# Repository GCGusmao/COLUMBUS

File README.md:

# COLUMBUS

README ainda em construção.

Desenvolvimento de um sistema de monitoramento para veículos híbridos, baseado em microcontrolador Atmel AVR. Foi desenvolvida a solução completa de hardware, software e soluções mecânicas.

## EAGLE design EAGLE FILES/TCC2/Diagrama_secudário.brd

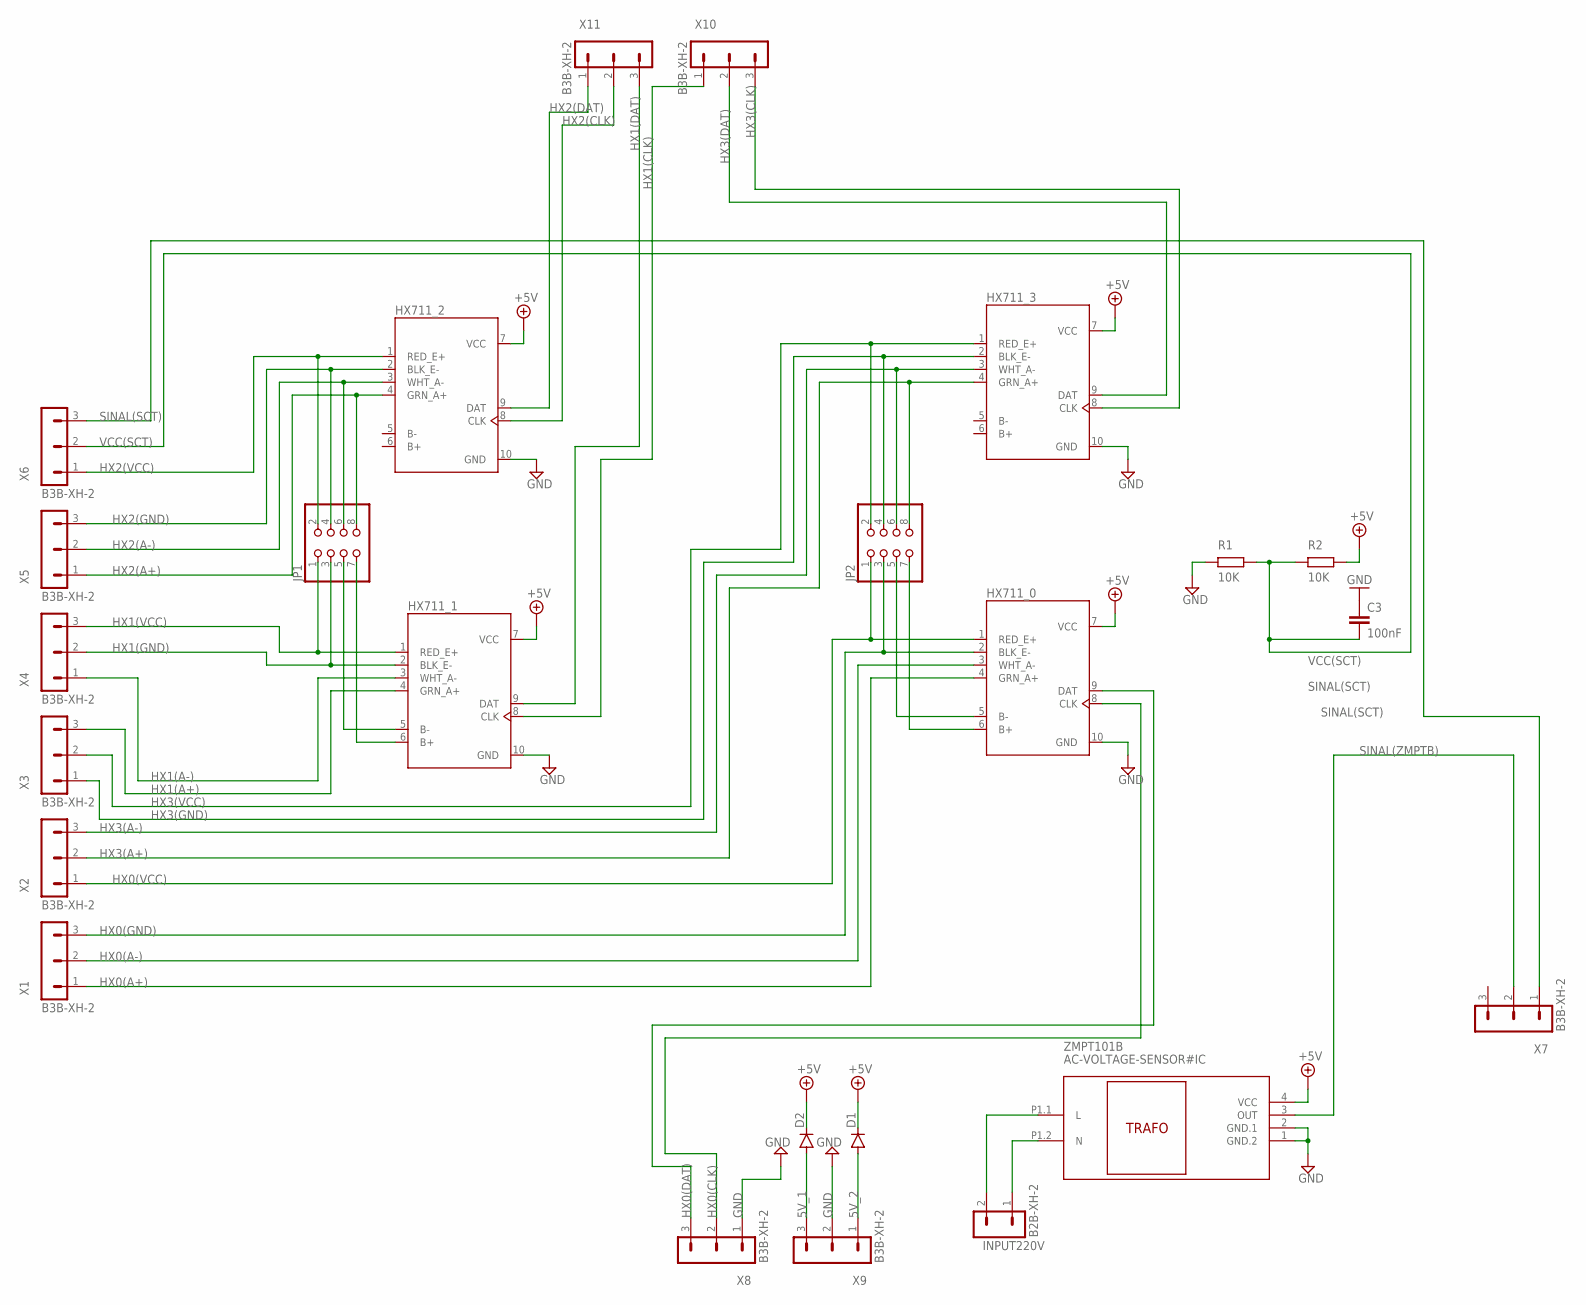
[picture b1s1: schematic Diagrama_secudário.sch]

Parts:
C3: 100nF; C050-025X075
D1: 1N4148DO35-7; DO35-7
D2: 1; DO35-7
HX711_0, HX711_1, HX711_2, HX711_3: HX711MODULO
INPUT220V: B2B-XH-2; B2B-XH-A
JP1, JP2: PINHD-2X4; 2X04
R1, R2: 10K; 1/4W-0.41K
X1, X2, X3, X4, X5, X6, X7, X8, X9, X10, X11: B3B-XH-2; B3B-XH-A
ZMPT101B: AC-VOLTAGE-SENSOR#IC

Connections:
5V_1: D2.A, X9.3
5V_2: D1.A, X9.1
+5V: D1.C, D2.C, HX711_0.7 (VCC), HX711_1.7 (VCC), HX711_2.7 (VCC), HX711_3.7 (VCC), R2.2, ZMPT101B.4 (VCC)
GND: C3.1, HX711_0.10 (GND), HX711_1.10 (GND), HX711_2.10 (GND), HX711_3.10 (GND), R1.1, X8.1, X9.2, ZMPT101B.1 (GND.2), ZMPT101B.2 (GND.1)
HX0(A+): HX711_0.4 (GRN_A+), X1.1
HX0(A-): HX711_0.3 (WHT_A-), X1.2
HX0(B+): HX711_0.6 (B+), JP2.7
HX0(B-): HX711_0.5 (B-), JP2.5
HX0(CLK): HX711_0.8 (CLK), X8.2
HX0(DAT): HX711_0.9 (DAT), X8.3
HX0(GND): HX711_0.2 (BLK_E-), JP2.3, X1.3
HX0(VCC): HX711_0.1 (RED_E+), JP2.1, X2.1
HX1(A+): HX711_1.4 (GRN_A+), X3.3
HX1(A-): HX711_1.3 (WHT_A-), X4.1
HX1(B+): HX711_1.6 (B+), JP1.7
HX1(B-): HX711_1.5 (B-), JP1.5
HX1(CLK): HX711_1.8 (CLK), X10.1
HX1(DAT): HX711_1.9 (DAT), X11.3
HX1(GND): HX711_1.2 (BLK_E-), JP1.3, X4.2
HX1(VCC): HX711_1.1 (RED_E+), JP1.1, X4.3
HX2(A+): HX711_2.4 (GRN_A+), JP1.8, X5.1
HX2(A-): HX711_2.3 (WHT_A-), JP1.6, X5.2
HX2(CLK): HX711_2.8 (CLK), X11.2
HX2(DAT): HX711_2.9 (DAT), X11.1
HX2(GND): HX711_2.2 (BLK_E-), JP1.4, X5.3
HX2(VCC): HX711_2.1 (RED_E+), JP1.2, X6.1
HX3(A+): HX711_3.4 (GRN_A+), JP2.8, X2.2
HX3(A-): HX711_3.3 (WHT_A-), JP2.6, X2.3
HX3(CLK): HX711_3.8 (CLK), X10.3
HX3(DAT): HX711_3.9 (DAT), X10.2
HX3(GND): HX711_3.2 (BLK_E-), JP2.4, X3.1
HX3(VCC): HX711_3.1 (RED_E+), JP2.2, X3.2
unnamed: INPUT220V.1, ZMPT101B.P1.2 (N)
unnamed: INPUT220V.2, ZMPT101B.P1.1 (L)
SINAL(SCT): X6.3, X7.1
SINAL(ZMPTB): X7.2, ZMPT101B.3 (OUT)
VCC(SCT): C3.2, R1.2, R2.1, X6.2

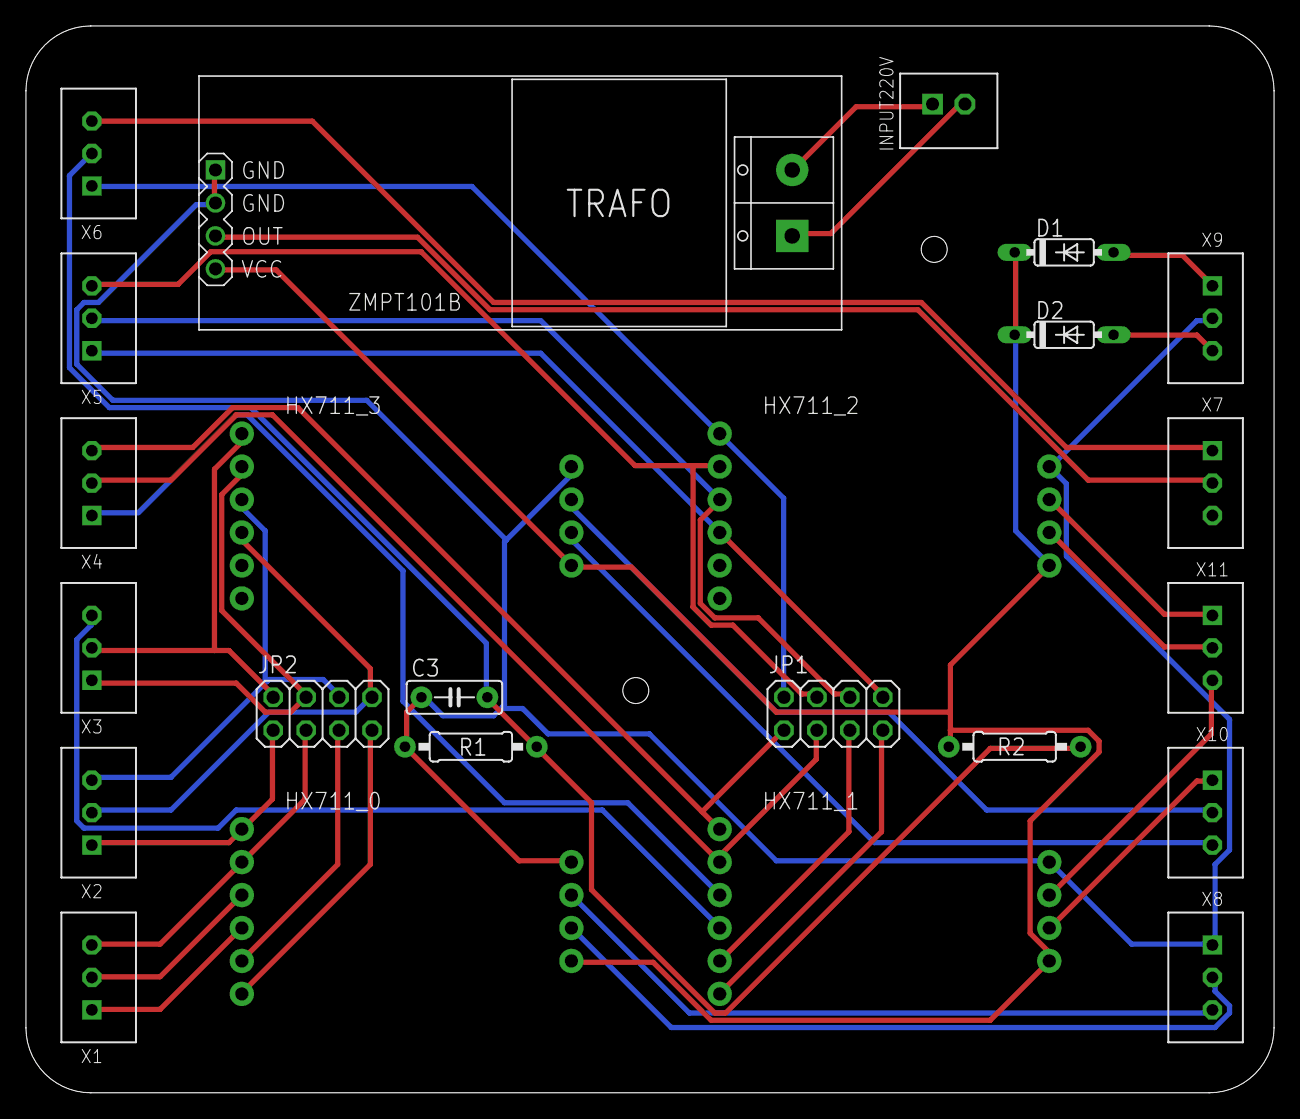
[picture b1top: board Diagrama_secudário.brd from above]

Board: 2 copper layers, 96.2 x 82.2 mm, 24 parts (0 on the bottom side), 37 nets.

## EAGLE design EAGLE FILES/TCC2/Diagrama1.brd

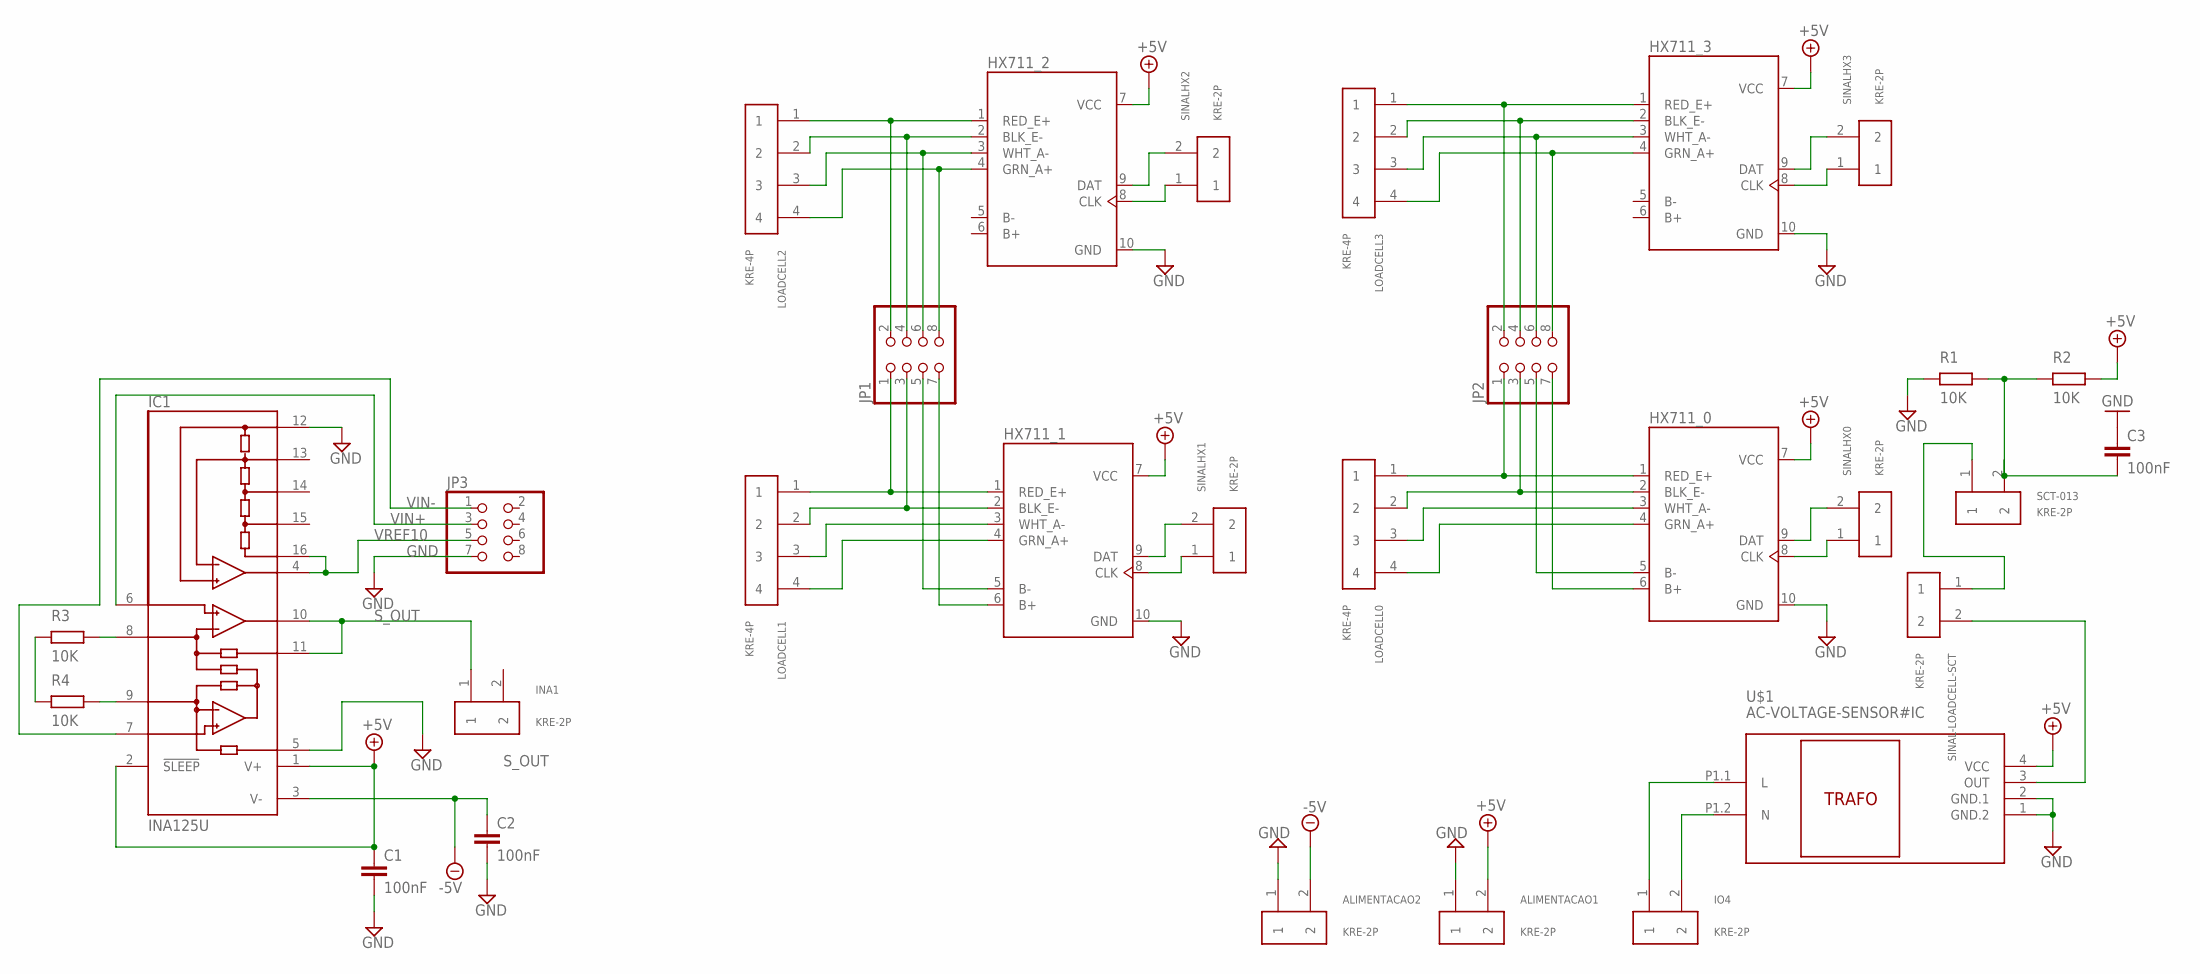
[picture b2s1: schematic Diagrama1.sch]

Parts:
ALIMENTACAO1, ALIMENTACAO2: KRE-2P
C1, C2, C3: 100nF; C050-025X075
HX711_0, HX711_1, HX711_2, HX711_3: HX711MODULO
IC1: INA125U; SO16-1
INA1: KRE-2P
IO4: KRE-2P
JP1, JP2, JP3: PINHD-2X4; 2X04
LOADCELL0, LOADCELL1, LOADCELL2, LOADCELL3: KRE-4P
R1, R2, R3, R4: 10K; 1/4W-0.41K
SCT-013: KRE-2P
SINAL-LOADCELL-SCT: KRE-2P
SINALHX0, SINALHX1, SINALHX2, SINALHX3: KRE-2P
U$1: AC-VOLTAGE-SENSOR#IC

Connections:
+5V: ALIMENTACAO1.2, C1.1, HX711_0.7 (VCC), HX711_1.7 (VCC), HX711_2.7 (VCC), HX711_3.7 (VCC), IC1.1 (V+), IC1.2 (!SLEEP), R2.2, U$1.4 (VCC)
-5V: ALIMENTACAO2.2, C2.1, IC1.3 (V-)
GND: ALIMENTACAO1.1, ALIMENTACAO2.1, C1.2, C2.2, C3.1, HX711_0.10 (GND), HX711_1.10 (GND), HX711_2.10 (GND), HX711_3.10 (GND), IC1.5 (REF), IC1.12 (REFCOM), JP3.7, R1.1, U$1.1 (GND.2), U$1.2 (GND.1)
unnamed: IO4.2, U$1.P1.2 (N)
unnamed: IO4.1, U$1.P1.1 (L)
unnamed: HX711_0.1 (RED_E+), JP2.1, LOADCELL0.1
unnamed: HX711_0.4 (GRN_A+), LOADCELL0.4
unnamed: HX711_0.2 (BLK_E-), JP2.3, LOADCELL0.2
unnamed: HX711_1.1 (RED_E+), JP1.1, LOADCELL1.1
unnamed: HX711_0.3 (WHT_A-), LOADCELL0.3
unnamed: HX711_1.2 (BLK_E-), JP1.3, LOADCELL1.2
unnamed: HX711_1.3 (WHT_A-), LOADCELL1.3
unnamed: C3.2, R1.2, R2.1, SCT-013.2
unnamed: HX711_0.9 (DAT), SINALHX0.2
unnamed: HX711_0.8 (CLK), SINALHX0.1
unnamed: HX711_1.5 (B-), JP1.5
unnamed: HX711_1.4 (GRN_A+), LOADCELL1.4
unnamed: SINAL-LOADCELL-SCT.2, U$1.3 (OUT)
unnamed: HX711_1.9 (DAT), SINALHX1.2
unnamed: HX711_1.8 (CLK), SINALHX1.1
unnamed: HX711_2.1 (RED_E+), JP1.2, LOADCELL2.1
unnamed: HX711_2.2 (BLK_E-), JP1.4, LOADCELL2.2
unnamed: HX711_2.3 (WHT_A-), JP1.6, LOADCELL2.3
unnamed: HX711_2.4 (GRN_A+), JP1.8, LOADCELL2.4
unnamed: HX711_2.9 (DAT), SINALHX2.2
unnamed: HX711_2.8 (CLK), SINALHX2.1
unnamed: HX711_3.1 (RED_E+), JP2.2, LOADCELL3.1
unnamed: HX711_3.2 (BLK_E-), JP2.4, LOADCELL3.2
unnamed: HX711_3.3 (WHT_A-), JP2.6, LOADCELL3.3
unnamed: HX711_3.4 (GRN_A+), JP2.8, LOADCELL3.4
unnamed: HX711_3.9 (DAT), SINALHX3.2
unnamed: HX711_3.8 (CLK), SINALHX3.1
unnamed: SCT-013.1, SINAL-LOADCELL-SCT.1
unnamed: HX711_1.6 (B+), JP1.7
unnamed: HX711_0.5 (B-), JP2.5
unnamed: HX711_0.6 (B+), JP2.7
unnamed: R3.1, R4.1
unnamed: IC1.9 (RG), R4.2
unnamed: IC1.8 (RG), R3.2
S_OUT: IC1.10 (OUT), IC1.11 (SENSE), INA1.1
VIN+: IC1.6 (+IN), JP3.3
VIN-: IC1.7 (-IN), JP3.1
VREF10: IC1.4 (REFOUT), IC1.16 (REF10), JP3.5

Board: 2 copper layers, 30 parts (0 on the bottom side), 43 nets, no tracks yet.

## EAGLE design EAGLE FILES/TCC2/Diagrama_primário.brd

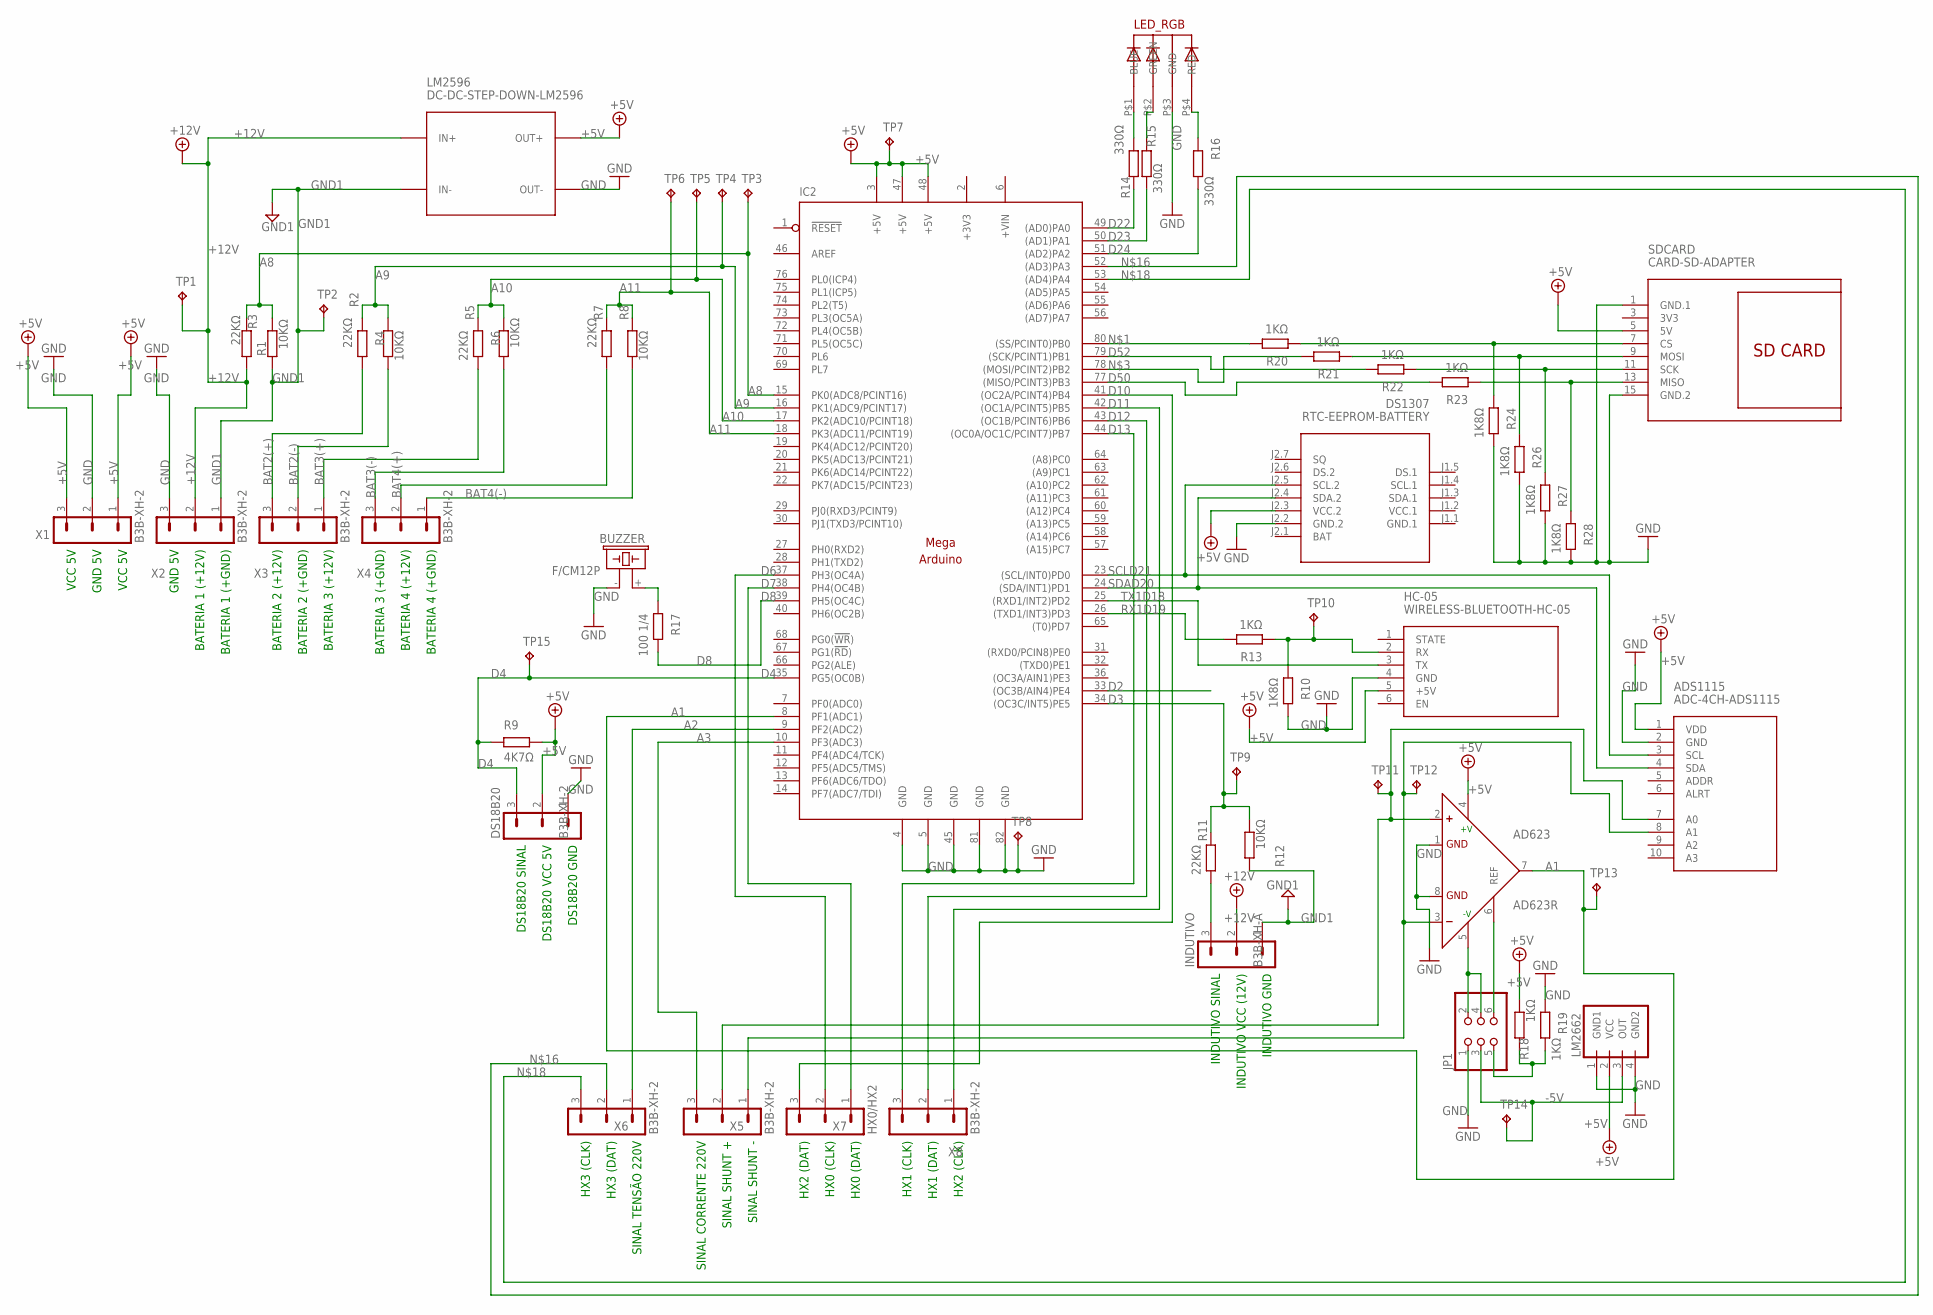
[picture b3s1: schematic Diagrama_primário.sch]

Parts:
AD623: AD623R; SO8
ADS1115: ADC-4CH-ADS1115
BUZZER: F/CM12P
DS18B20: B3B-XH-2; B3B-XH-A
DS1307: RTC-EEPROM-BATTERY
HC-05: WIRELESS-BLUETOOTH-HC-05
IC2: MEGAARDUINO_11; MEGA_ARDUINO_1
INDUTIVO: B3B-XH-A
JP1: PINHD-2X3; 2X03
LED_RGB: 5MMRGBLED; LED5MMRGB
LM2596: DC-DC-STEP-DOWN-LM2596
LM2662: LM2662
R1, R4, R6, R8, R12: 10KΩ; 1/4W-0.41K
R2, R3, R5, R7, R11: 22KΩ; 1/4W-0.41K
R9: 4K7Ω; 1/4W-0.41K
R10, R24, R26, R27, R28: 1K8Ω; 1/4W-0.41K
R13, R18, R19, R20, R21, R22, R23: 1KΩ; 1/4W-0.41K
R14, R15, R16: 330Ω; 1/4W-0.41K
R17: 100 1/4; 1/4W-0.41K
SDCARD: CARD-SD-ADAPTER
TP1, TP2, TP3, TP4, TP5, TP6, TP7, TP8, TP9, TP10, TP11, TP12, TP13, TP14, TP15: TPB1,27; B1,27
X1, X2, X3, X4, X5, X6, X8: B3B-XH-2; B3B-XH-A
X7: HX0/HX2; B3B-XH-A

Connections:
3V3: SDCARD.3 (3V3)
+3V3: IC2.2 (+3V3)
+5V: AD623.4 (+V), ADS1115.1 (VDD), DS18B20.2, DS1307.J2.3 (VCC.2), HC-05.5 (+5V), IC2.3 (+5V), IC2.47 (+5V), IC2.48 (+5V), LM2596.OUT+, LM2662.2 (VCC), R9.2, R18.1, SDCARD.5 (5V), TP7.TP, X1.1, X1.3
+12V: INDUTIVO.2, LM2596.IN+, R3.2, TP1.TP, X2.2
+VIN: IC2.6 (+VIN)
-5V: JP1.3, LM2662.3 (OUT), TP14.TP
A1: AD623.7 (OUT), IC2.8 (PF1(ADC1)), TP13.TP
A2: IC2.9 (PF2(ADC2)), X6.1
A3: IC2.10 (PF3(ADC3)), X5.3
A8: IC2.15 (PK0(ADC8/PCINT16)), R1.1, R3.1, TP3.TP
A9: IC2.16 (PK1(ADC9/PCINT17)), R2.1, R4.1, TP4.TP
A10: IC2.17 (PK2(ADC10/PCINT18)), R5.1, R6.1, TP5.TP
A11: IC2.18 (PK3(ADC11/PCINT19)), R7.1, R8.1, TP6.TP
BAT2(+): R2.2, X3.3
BAT2(-): R4.2, X3.2
BAT3(+): R5.2, X3.1
BAT3(-): R6.2, X4.3
BAT4(+): R7.2, X4.2
BAT4(-): R8.2, X4.1
D2: IC2.33 ((OC3B/AIN4)PE4)
D3: IC2.34 ((OC3C/INT5)PE5), R11.1, R12.1, TP9.TP
D4: DS18B20.3, IC2.35 (PG5(OC0B)), R9.1, TP15.TP
D6: IC2.37 (PH3(OC4A)), X7.2
D7: IC2.38 (PH4(OC4B)), X7.1
D8: IC2.39 (PH5(OC4C)), R17.2
D10: IC2.41 ((OC2A/PCINT4)PB4), X7.3
D11: IC2.42 ((OC1A/PCINT5)PB5), X8.1
D12: IC2.43 ((OC1B/PCINT6)PB6), X8.2
D13: IC2.44 ((OC0A/OC1C/PCINT7)PB7), X8.3
D22: IC2.49 ((AD0)PA0), R14.2
D23: IC2.50 ((AD1)PA1), R15.2
D24: IC2.51 ((AD2)PA2), R16.2
D50: IC2.77 ((MISO/PCINT3)PB3), R23.2
D51: R21.1, R26.1, SDCARD.9 (MOSI)
D52: IC2.79 ((SCK/PCINT1)PB1), R22.2
D53: R20.1, R24.1, SDCARD.7 (CS)
GND: AD623.1 (RG), AD623.8 (RG), ADS1115.2 (GND), BUZZER.- (2), DS18B20.1, DS1307.J2.2 (GND.2), HC-05.4 (GND), IC2.4 (GND), IC2.5 (GND), IC2.45 (GND), IC2.81 (GND), IC2.82 (GND), JP1.1, LED_RGB.P$3 (GND), LM2596.OUT-, LM2662.1 (GND1), LM2662.4 (GND2), R10.2, R19.1, R24.2, R26.2, R27.2, R28.2, SDCARD.1 (GND.1), SDCARD.15 (GND.2), TP8.TP, X1.2, X2.3
GND1: INDUTIVO.1, LM2596.IN-, R1.2, R12.2, TP2.TP, X2.1
GND.1: DS1307.J1.1 (GND.1)
unnamed: IC2.80 ((SS/PCINT0)PB0), R20.2
unnamed: INDUTIVO.3, R11.2
unnamed: IC2.78 ((MOSI/PCINT2)PB2), R21.2
unnamed: HC-05.2 (RX), R10.1, R13.1, TP10.TP
unnamed: LED_RGB.P$1 (BLUE), R14.1
unnamed: LED_RGB.P$2 (GREEN), R15.1
unnamed: LED_RGB.P$4 (RED), R16.1
unnamed: R22.1, R27.1, SDCARD.11 (SCK)
unnamed: R23.1, R28.1, SDCARD.13 (MISO)
unnamed: IC2.52 ((AD3)PA3), X6.2
unnamed: BUZZER.+ (1), R17.1
unnamed: IC2.53 ((AD4)PA4), X6.3
unnamed: AD623.3 (-), ADS1115.8 (A1), TP12.TP, X5.1
unnamed: AD623.2 (+), ADS1115.7 (A0), TP11.TP, X5.2
unnamed: AD623.5 (-V), JP1.2, JP1.4
unnamed: AD623.6 (REF), JP1.6
RX1D19: IC2.26 ((TXD1/INT3)PD3), R13.2
SCLD21: ADS1115.3 (SCL), DS1307.J2.5 (SCL.2), IC2.23 ((SCL/INT0)PD0)
SDAD20: ADS1115.4 (SDA), DS1307.J2.4 (SDA.2), IC2.24 ((SDA/INT1)PD1)
TX1D18: HC-05.3 (TX), IC2.25 ((RXD1/INT2)PD2)
VCC1: JP1.5, R18.2, R19.2
VCC.1: DS1307.J1.2 (VCC.1)

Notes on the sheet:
SINAL CORRENTE 220V
SINAL SHUNT +
SINAL SHUNT -
HX3 (CLK)
SINAL TENSÃO 220V
HX2 (DAT)
HX0 (CLK)
HX0 (DAT)
HX1 (CLK)
HX1 (DAT)
HX2 (CLK)
INDUTIVO SINAL
INDUTIVO VCC (12V)
INDUTIVO GND
DS18B20 SINAL
DS18B20 VCC 5V
DS18B20 GND
VCC 5V
GND 5V
BATERIA 1 (+12V)
BATERIA 1 (+GND)
BATERIA 2 (+12V)
BATERIA 2 (+GND)
BATERIA 3 (+12V)
BATERIA 3 (+GND)
BATERIA 4 (+12V)
BATERIA 4 (+GND)
HX3 (DAT)

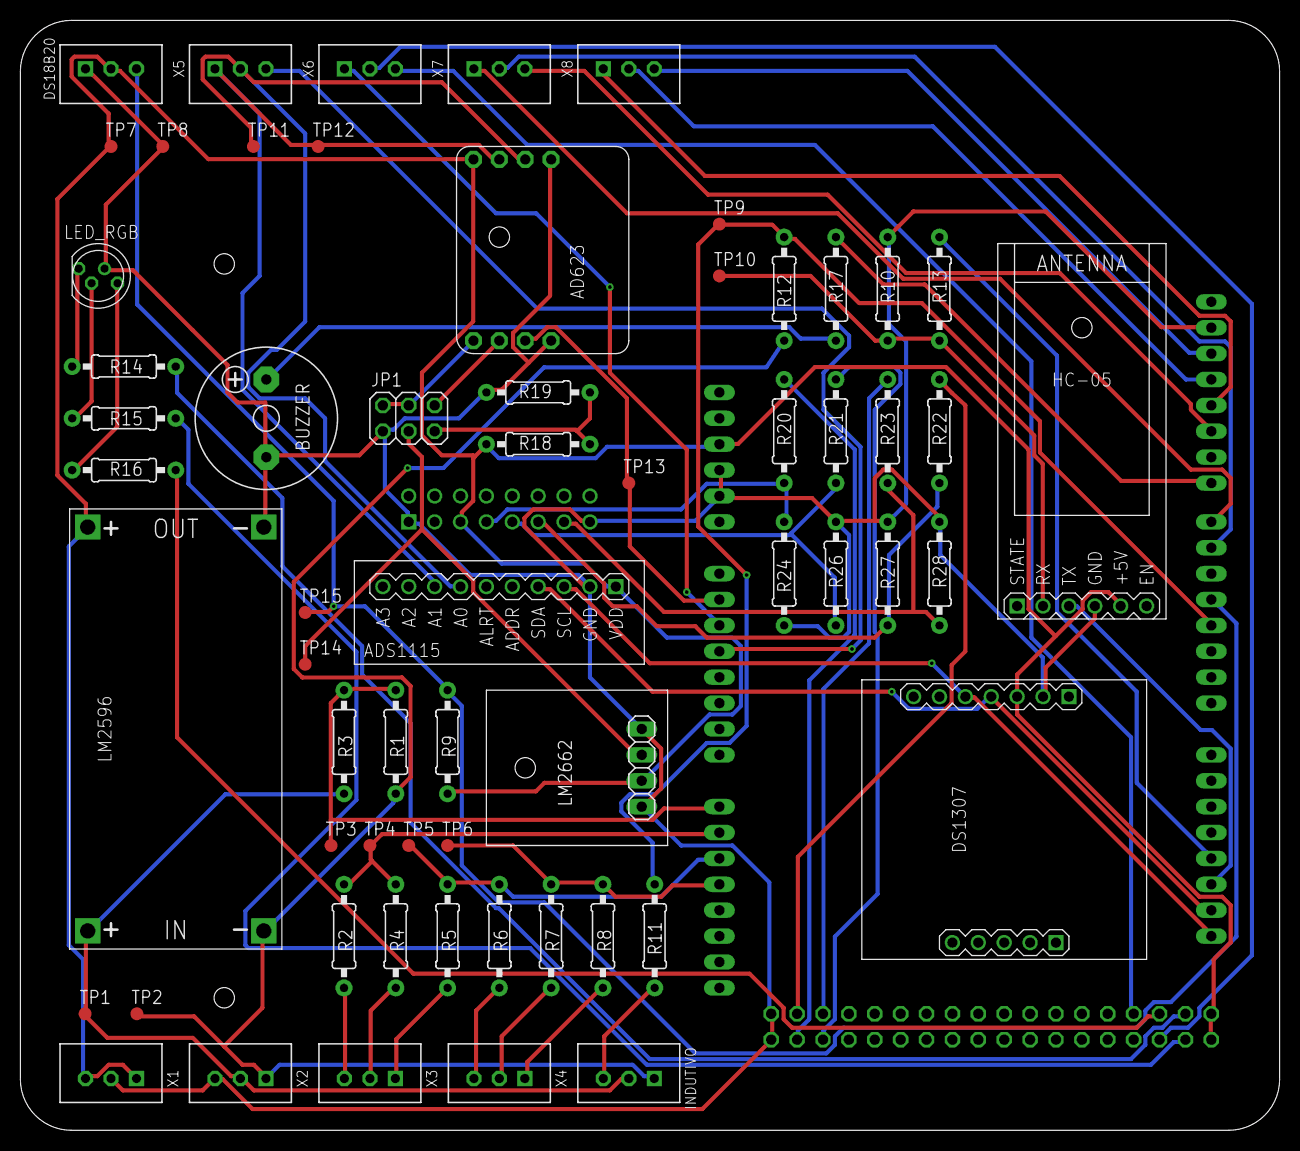
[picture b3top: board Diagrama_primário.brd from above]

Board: 2 copper layers, 123.5 x 108.9 mm, 63 parts (0 on the bottom side), 55 nets.

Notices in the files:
parts and their libraries:
diy-modules: Released under the Creative Commons Attribution 4.0 International License: http://creativecommons.org/licenses/by/4.0
